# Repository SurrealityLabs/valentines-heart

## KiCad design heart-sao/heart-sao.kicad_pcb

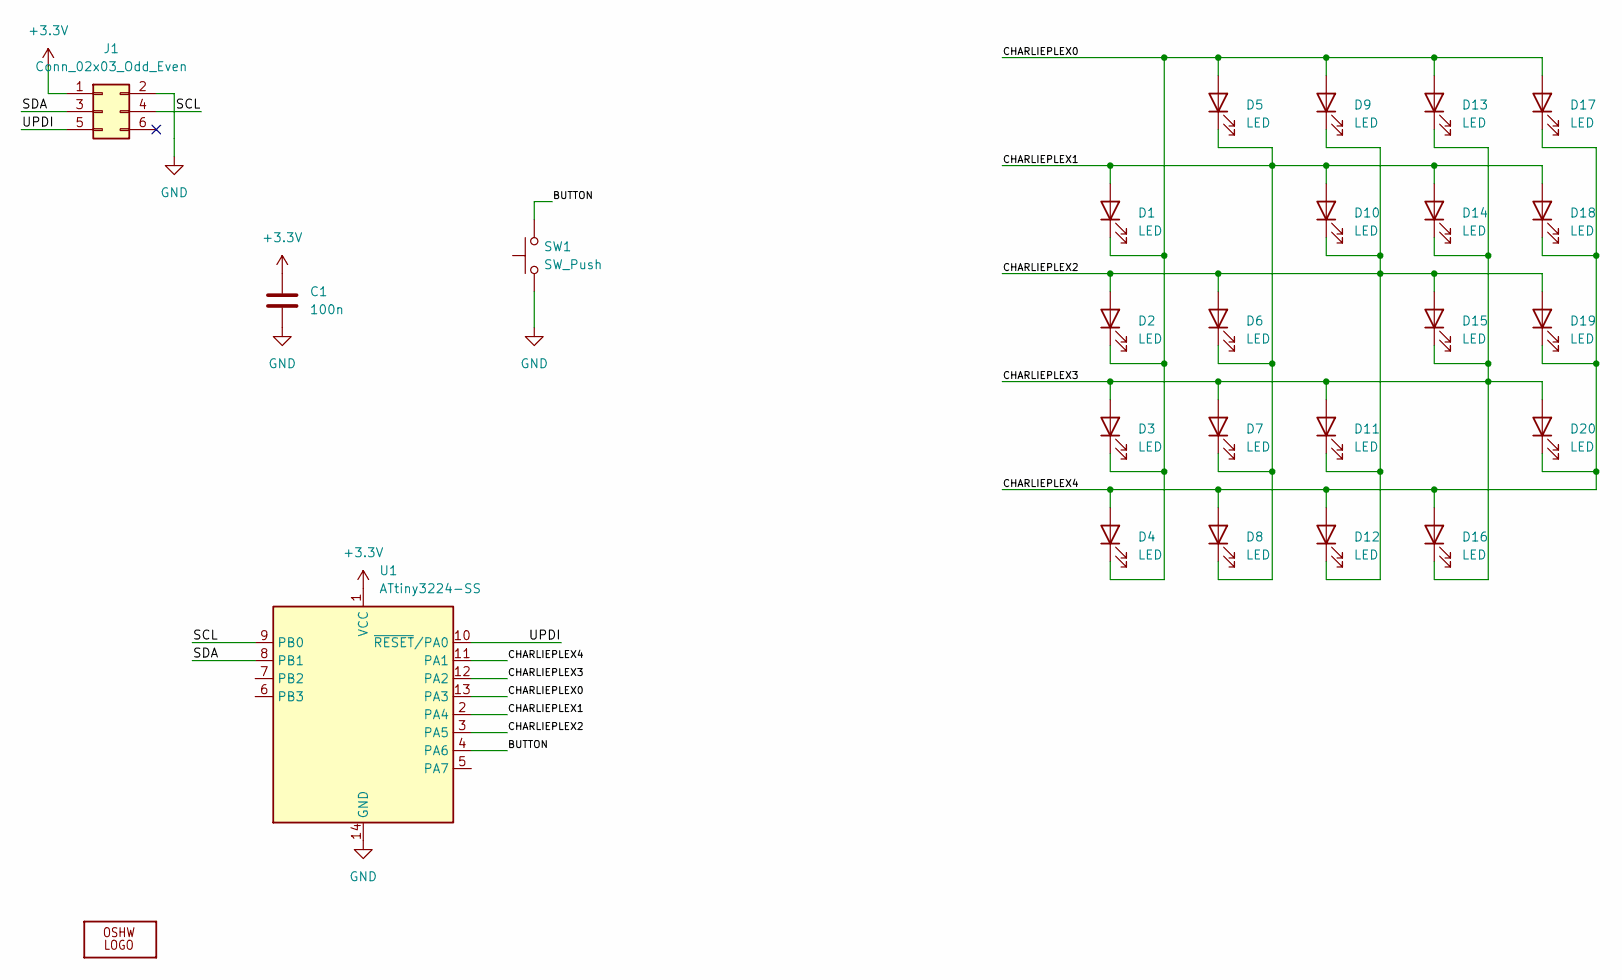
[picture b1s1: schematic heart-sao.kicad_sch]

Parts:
C1: 100n; C_1206_3216Metric
D1, D2, D3, D4, D5, D6, D7, D8, D9, D10, D11, D12, D13, D14, D15, D16, D17, D18, D19, D20: LED; LED_1206_3216Metric
J1: Conn_02x03_Odd_Even; IDC-Header_2x03_P2.54mm_Vertical_SMD
LOGO1: OSHW_LOGO_FILLX0100-NT; OSHW_FILLX100_NOTEXT
SW1: SW_Push; SW_SPST_CK_RS282G05A3
U1: ATtiny3224-SS; SOIC-14_3.9x8.7mm_P1.27mm

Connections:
+3.3V: C1.1, J1.1, U1.1 (VCC)
/BUTTON: SW1.2, U1.4 (PA6)
/CHARLIEPLEX0: D1.1 (K), D2.1 (K), D3.1 (K), D4.1 (K), D5.2 (A), D9.2 (A), D13.2 (A), D17.2 (A), U1.13 (PA3)
/CHARLIEPLEX1: D1.2 (A), D5.1 (K), D6.1 (K), D7.1 (K), D8.1 (K), D10.2 (A), D14.2 (A), D18.2 (A), U1.2 (PA4)
/CHARLIEPLEX2: D2.2 (A), D6.2 (A), D9.1 (K), D10.1 (K), D11.1 (K), D12.1 (K), D15.2 (A), D19.2 (A), U1.3 (PA5)
/CHARLIEPLEX3: D3.2 (A), D7.2 (A), D11.2 (A), D13.1 (K), D14.1 (K), D15.1 (K), D16.1 (K), D20.2 (A), U1.12 (PA2)
/CHARLIEPLEX4: D4.2 (A), D8.2 (A), D12.2 (A), D16.2 (A), D17.1 (K), D18.1 (K), D19.1 (K), D20.1 (K), U1.11 (PA1)
/SCL: J1.4, U1.9 (PB0)
/SDA: J1.3, U1.8 (PB1)
/UPDI: J1.5, U1.10 (~RESET/PA0)
GND: C1.2, J1.2, SW1.1, U1.14 (GND)

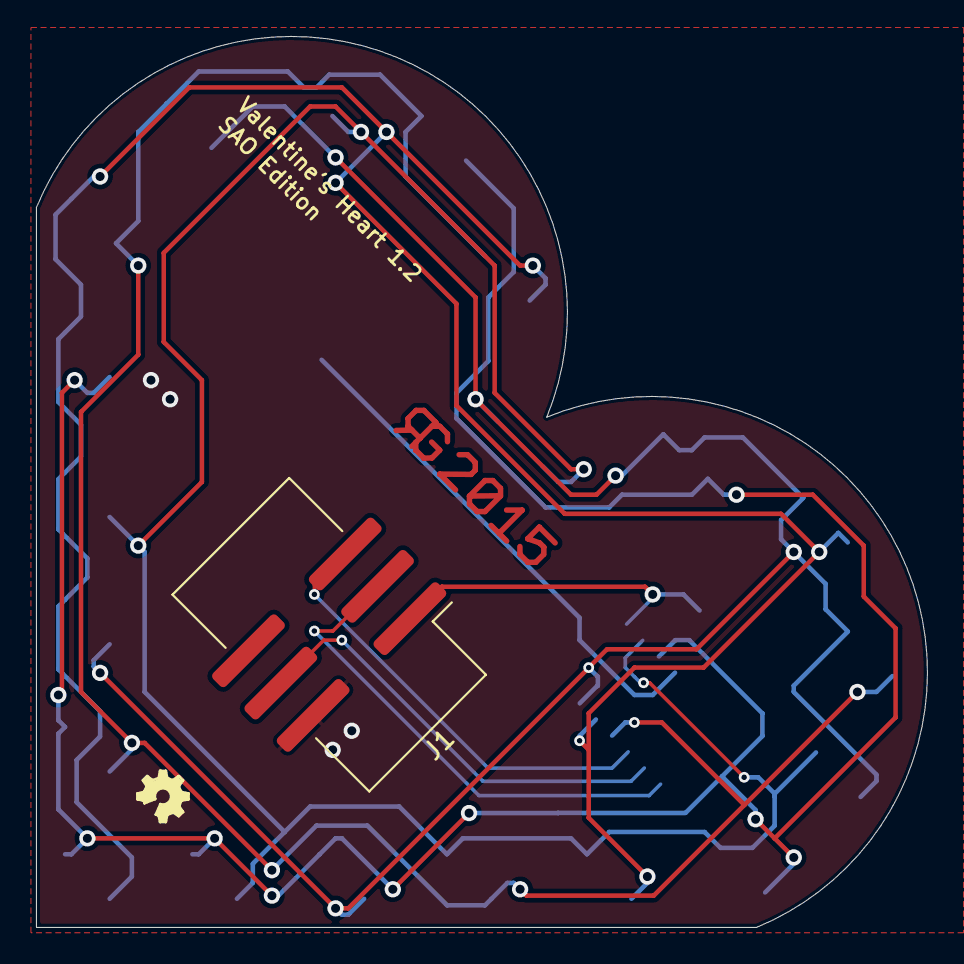
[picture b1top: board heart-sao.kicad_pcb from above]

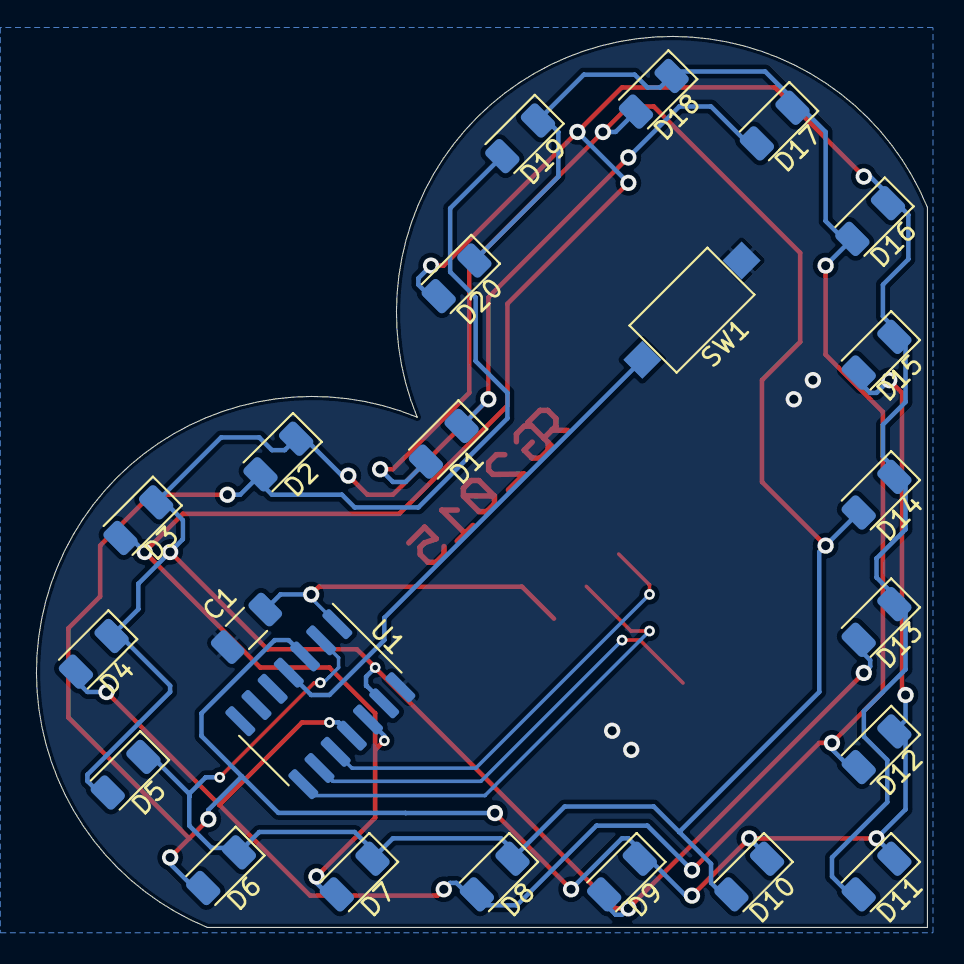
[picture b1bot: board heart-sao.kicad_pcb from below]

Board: 2 copper layers, 49.5 x 49.5 mm, 26 parts (23 on the bottom side), 11 nets.

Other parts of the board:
U$1: RGLOGO_SMALL_2015

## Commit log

2013-12-18 Adding .hgignore
2013-12-18 Adding final rev of PCB
2013-12-18 Adding 3D rendering of board
2013-12-31 Adding first rev of PCB
2013-12-31 Adding first rev of code - UNTESTED
2014-01-11 Adding code support for internal pullup resistor and improved pattern timing
2014-01-11 Adding Rev. 1.1 hardware to correct DRC error and add cathode markers for LEDs
2015-08-07 Adding punk editions (SMD parts)
2023-11-05 Adding KiCad version
2023-11-05 Updating layout
2023-11-05 Adding SAO version of heart board
